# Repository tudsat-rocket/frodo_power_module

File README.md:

# Power Board

The battery board in our rockets.

### Components

- 3x 3000 mA h Sony VTC6 18650 lithium-ion cells in series

### Usage

| Connector           | Purpose                                                         |
| -----------         | --------------------------------------------------------------- |
| main switch         | + and - needs to be connected to enable the output on HC1, 2, 3 |
| HC1, 2, 3           | Power output                                                    |
| circumvent          | short + and - to supply power to Vmain without batteries directly from charge voltage |
| Vehicle Bus 1, 2    | Communication and bus power supply                              |

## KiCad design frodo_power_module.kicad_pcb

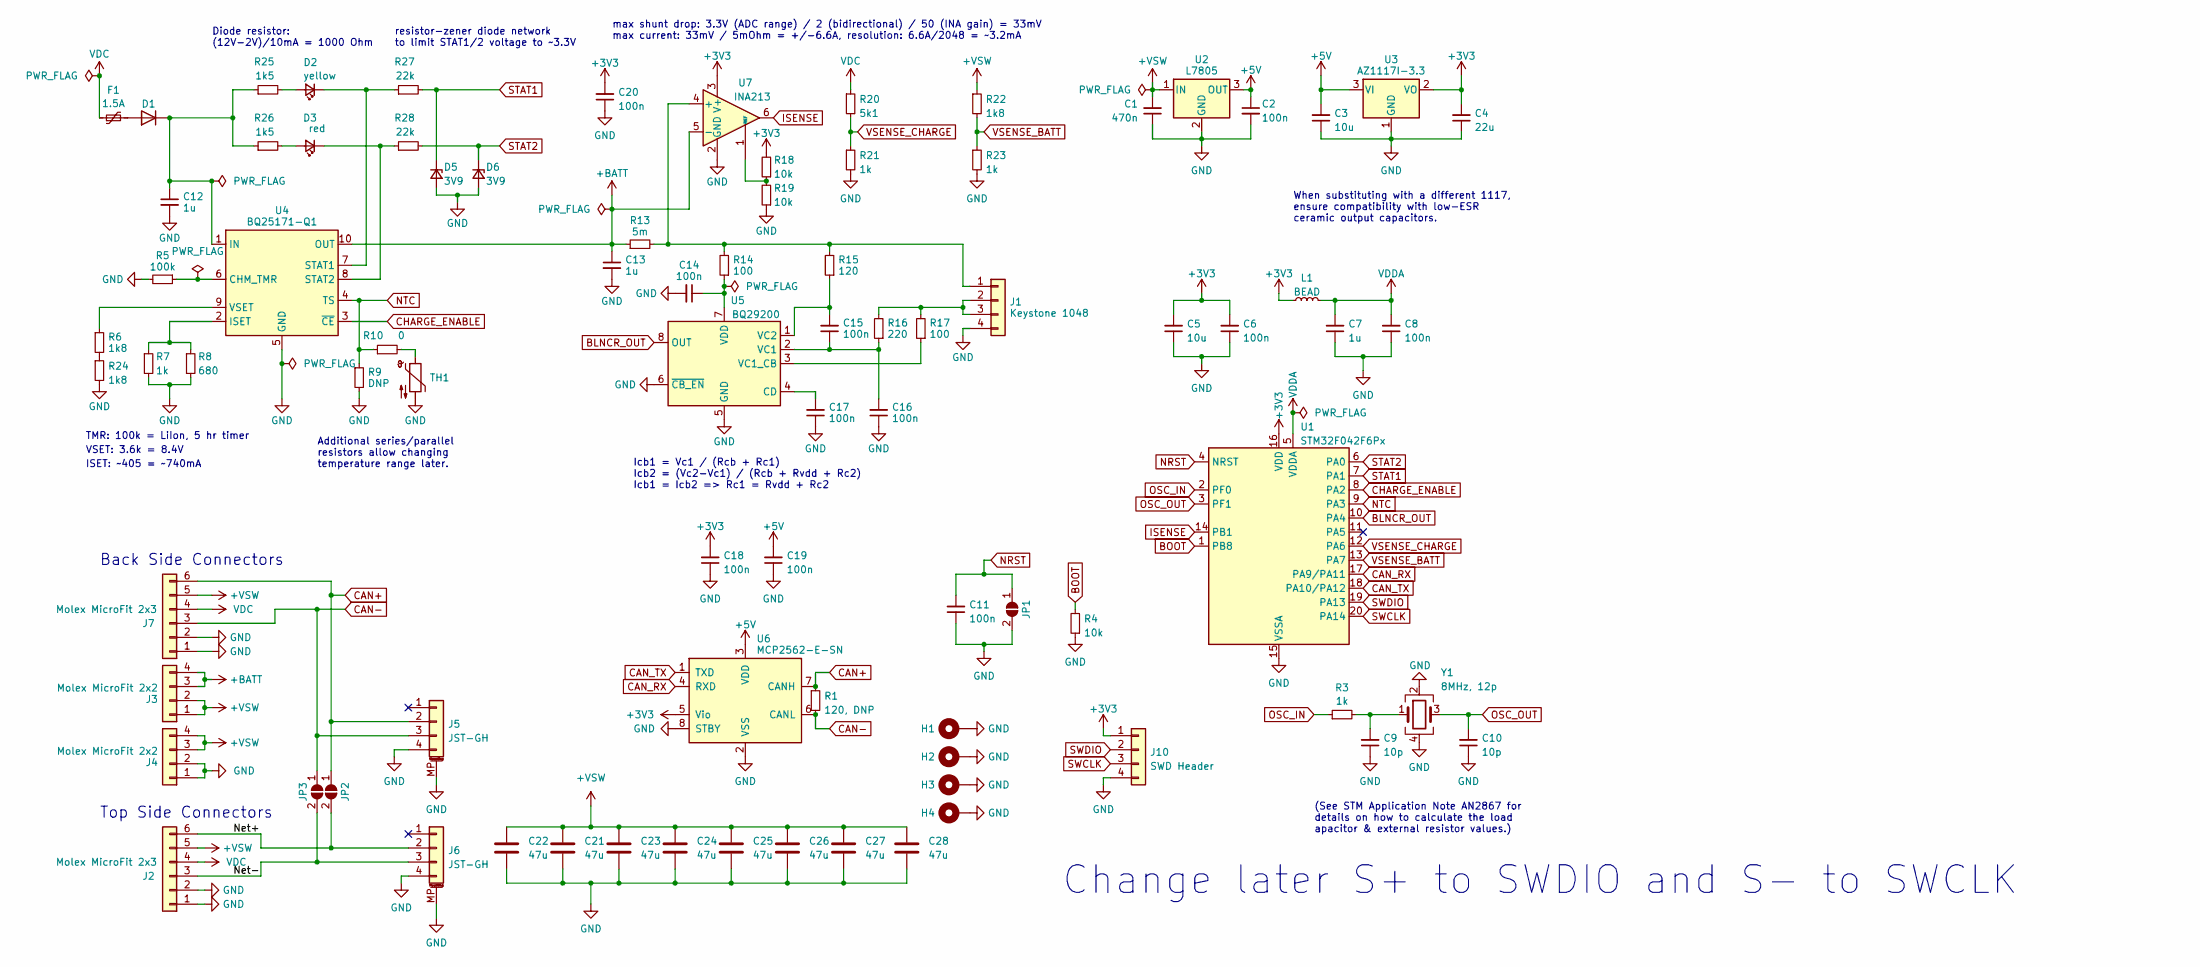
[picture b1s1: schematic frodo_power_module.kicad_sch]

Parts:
C1: 470n; C_0603_1608Metric; Part# CL10B474KA8NNNC; LCSC# C1623
C2, C6, C8, C11, C14, C15, C16, C17, C18, C19, C20: 100n; C_0603_1608Metric; Part# CC0603KRX7R9BB104; LCSC# C14663
C3, C5: 10u; C_1206_3216Metric; Part# CL31A106KBHNNNE; LCSC# C13585
C4: 22u; C_1206_3216Metric; Part# CL31A226KAHNNNE; LCSC# C12891
C7, C12, C13: 1u; C_0805_2012Metric; Part# CL21B105KBFNNNE; LCSC# C28323
C9, C10: 10p; C_0603_1608Metric; Part# CL10C100JB8NNNC; LCSC# C1634
C21, C22, C23, C24, C25, C26, C27, C28: 47u; C_1206_3216Metric
D1: D_SMA; Part# SS54; DigiKey# SK34A-LTPMSCT-ND
D2: yellow; LED_0603_1608Metric; Part# 19-213/Y2C-CQ2R2L/3T(CY); LCSC# C72038
D3: red; LED_0603_1608Metric; Part# KT-0603R; LCSC# C2286
D5, D6: 3V9; SOD323F_DIO; Part# D3Z3V9BF-7; LCSC# C444415
F1: 1.5A; Fuse_1206_3216Metric; Part# 0ZCJ0075AF2E; DigiKey# 507-1805-1-ND
H1, H2, H3, H4: MountingHole_Pad; MountingHole_3.2mm_M3_Pad_Via; Part# N/A; DigiKey# N/A
J1: Keystone 1048; keystone_1048; Part# 1048; DigiKey# 36-1098-ND
J2, J7: Molex MicroFit 2x3; Molex_Micro-Fit_3.0_43045-0600_2x03_P3.00mm_Horizontal; Part# 0430450600; LCSC# C127367
J3, J4: Molex MicroFit 2x2; Molex_Micro-Fit_3.0_43045-0400_2x02_P3.00mm_Horizontal; Part# 0430450400; LCSC# C122413
J5, J6: JST-GH; JST_GH_SM04B-GHS-TB_1x04-1MP_P1.25mm_Horizontal; Part# SM04B-GHS-TB; LCSC# C189895
J10: SWD Header; PinHeader_1x04_P2.54mm_Vertical; Part# N/A; DigiKey# N/A
JP1, JP2, JP3: r; SolderJumper-2_P1.3mm_Open_RoundedPad1.0x1.5mm; Part# N/A; DigiKey# N/A
L1: BEAD; L_0603_1608Metric; Part# GZ1608D601TF; LCSC# C1002
R1: 120, DNP; R_0603_1608Metric; Part# 0603WAF1200T5E; LCSC# C22787
R3, R7, R21, R23: 1k; R_0603_1608Metric; Part# 0603WAF1001T5E; LCSC# C21190
R4, R18, R19: 10k; R_0603_1608Metric; Part# 0603WAF1002T5E; LCSC# C25804
R5: 100k; R_0603_1608Metric; Part# 0603WAF1003T5E; LCSC# C25803
R6, R22, R24: 1k8; R_0603_1608Metric; Part# 0603WAF1801T5E; LCSC# C4177
R8: 680; R_0603_1608Metric; Part# 0603WAF6800T5E; LCSC# C23228
R9: DNP; R_0603_1608Metric; Part# N/A; LCSC# N/A
R10: 0; R_0603_1608Metric; Part# 0603WAF0000T5E; LCSC# C21189
R13: 5m; R_2512_6332Metric; Part# PA2512FKE7W0R005E; LCSC# C723630
R14, R17: 100; R_0603_1608Metric; Part# 0603WAF1000T5E; LCSC# C22775
R15: 120; R_0603_1608Metric; Part# 0603WAF1200T5E; LCSC# C22787
R16: 220; R_0603_1608Metric; Part# 0603WAF2200T5E; LCSC# C22962
R20: 5k1; R_0603_1608Metric; Part# 0603WAF5101T5E; LCSC# C23186
R25, R26: 1k5; R_0603_1608Metric; Part# 0603WAF1501T5E; LCSC# C22843
R27, R28: 22k; R_0603_1608Metric; Part# 0603WAF2202T5E; LCSC# C31850
TH1: NCU18XH103F6SRB; R_0603_1608Metric; Part# NCU18XH103F6SRB; DigiKey# 490-18139-1-ND
U1: STM32F042F6Px; TSSOP-20_4.4x6.5mm_P0.65mm; Part# STM32F042F6P6TR; DigiKey# 497-19656-1-ND
U2: L7805; TO-252-2; Part# L78M05ABDT-TR; LCSC# C58069
U3: AZ1117I-3.3; SOT-223-3_TabPin2; Part# AZ1117CH-3.3TRG1; LCSC# C92102
U4: BQ25171-Q1; Texas_S-PVSON-N10_ThermalVias; Part# BQ25171QWDRCRQ1; DigiKey# 296-BQ25171QWDRCRQ1CT-ND
U5: BQ29200; Texas_S-PVSON-N8_ThermalVias; Part# BQ29200DRBT; DigiKey# 296-32038-1-ND
U6: MCP2562-E-SN; SOIC-8_3.9x4.9mm_P1.27mm; Part# MCP2562-H/SN; DigiKey# MCP2562-H/SN
U7: INA213; SOT-363_SC-70-6; Part# INA213AIDCKR; DigiKey# 296-26072-1-ND
Y1: 8MHz, 12p; Crystal_SMD_5032-4Pin_5.0x3.2mm; Part# 5TJ480000NYLBC; DigiKey# 50-ECS-80-12-33-JGN-CT-ND

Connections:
+3V3: C4.2, C5.2, C6.2, C18.2, C20.2, J10.1, L1.1, R18.2, U1.16 (VDD), U3.2 (VO), U6.5 (Vio), U7.3 (V+)
+5V: C2.1, C3.2, C19.2, U2.3 (OUT), U3.3 (VI), U6.3 (VDD)
+BATT: C13.1, J3.3, J3.4, R13.1, U4.10 (OUT), U7.5 (-)
+VSW: C1.2, C21.1, C22.1, C23.1, C24.1, C25.1, C26.1, C27.1, C28.1, J2.5, J3.1, J3.2, J4.3, J4.4, J7.5, R22.1, U2.1 (IN)
/Net+: J2.6, J6.2, JP2.2 (B)
/Net-: J2.3, J6.3, JP3.2 (B)
BLNCR_OUT: U1.10 (PA4), U5.8 (OUT)
BOOT: R4.2, U1.1 (PB8)
CAN+: J5.2, J7.6, JP2.1 (A), R1.1, U6.7 (CANH)
CAN-: J5.3, J7.3, JP3.1 (A), R1.2, U6.6 (CANL)
CAN_RX: U1.17 (PA9/PA11), U6.4 (RXD)
CAN_TX: U1.18 (PA10/PA12), U6.1 (TXD)
CHARGE_ENABLE: U1.8 (PA2), U4.3 (~CE)
GND: C1.1, C2.2, C3.1, C4.1, C5.1, C6.1, C7.1, C8.1, C9.1, C10.1, C11.1, C12.2, C13.2, C14.2, C16.1, C17.1, C18.1, C19.1, C20.1, C21.2, C22.2, C23.2, C24.2, C25.2, C26.2, C27.2, C28.2, D5.2 (A), D6.2 (A), H1.1, H2.1, H3.1, H4.1, J1.4, J2.1, J2.2, J4.1, J4.2, J5.4, J5.MP (MountPin), J6.4, J6.MP (MountPin), J7.1, J7.2, J10.4, JP1.2 (B), R4.1, R5.2, R7.2, R8.2, R9.2, R19.1, R21.2, R23.2, R24.2, TH1.2, U1.15 (VSSA), U2.2 (GND), U3.1 (GND), U4.5 (GND), U4.11 (GND), U5.5 (GND), U5.6 (~CB_EN), U5.9 (PWR_PAD), U6.2 (VSS), U6.8 (STBY), U7.2 (GND), Y1.2, Y1.4
ISENSE: U1.14 (PB1), U7.6
NRST: C11.2, JP1.1 (A), U1.4 (NRST)
NTC: R9.1, R10.1, U1.9 (PA3), U4.4 (TS)
unnamed: C9.2, R3.2, Y1.1
unnamed: D1.2 (A), F1.2
unnamed: C12.1, D1.1 (K), R25.1, R26.1, U4.1 (IN)
unnamed: D2.2 (A), R25.2
unnamed: D2.1 (K), R27.1, U4.7 (STAT1)
unnamed: D3.2 (A), R26.2
unnamed: D3.1 (K), R28.1, U4.8 (STAT2)
unnamed: J1.1, R13.2, R14.2, R15.2, U7.4 (+)
unnamed: J1.2, J1.3, R16.2, R17.2
unnamed: R10.2, TH1.1
unnamed: R6.2, R24.1
unnamed: R5.1, U4.6 (CHM_TMR)
unnamed: R7.1, R8.1, U4.2 (ISET)
unnamed: R6.1, U4.9 (VSET)
unnamed: C17.2, U5.4 (CD)
unnamed: C15.1, C16.2, R16.1, U5.2 (VC1)
unnamed: R17.1, U5.3 (VC1_CB)
unnamed: C15.2, R15.1, U5.1 (VC2)
unnamed: C14.1, R14.1, U5.7 (VDD)
unnamed: R18.1, R19.2, U7.1 (REF)
OSC_IN: R3.1, U1.2 (PF0)
OSC_OUT: C10.2, U1.3 (PF1), Y1.3
STAT1: D5.1 (K), R27.2, U1.7 (PA1)
STAT2: D6.1 (K), R28.2, U1.6 (PA0)
SWCLK: J10.3, U1.20 (PA14)
SWDIO: J10.2, U1.19 (PA13)
VDC: F1.1, J2.4, J7.4, R20.1
VDDA: C7.2, C8.2, L1.2, U1.5 (VDDA)
VSENSE_BATT: R22.2, R23.1, U1.13 (PA7)
VSENSE_CHARGE: R20.2, R21.1, U1.12 (PA6)

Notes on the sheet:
(See STM Application Note AN2867 for details on how to calculate the load apacitor & external resistor values.)
Diode resistor: (12V-2V)/10mA = 1000 Ohm
Icb1 = Vc1 / (Rcb + Rc1) Icb2 = (Vc2-Vc1) / (Rcb + Rvdd + Rc2) Icb1 = Icb2 => Rc1 = Rvdd + Rc2
When substituting with a different 1117, ensure compatibility with low-ESR ceramic output capacitors.
max shunt drop: 3.3V (ADC range) / 2 (bidirectional) / 50 (INA gain) = 33mV max current: 33mV / 5mOhm = +/-6.6A, resolution: 6.6A/2048 = ~3.2mA
TMR: 100k = LiIon, 5 hr timer
Top Side Connectors
Back Side Connectors
VSET: 3.6k = 8.4V
Change later S+ to SWDIO and S- to SWCLK
Additional series/parallel resistors allow changing temperature range later.
ISET: ~405 = ~740mA
resistor-zener diode network to limit STAT1/2 voltage to ~3.3V

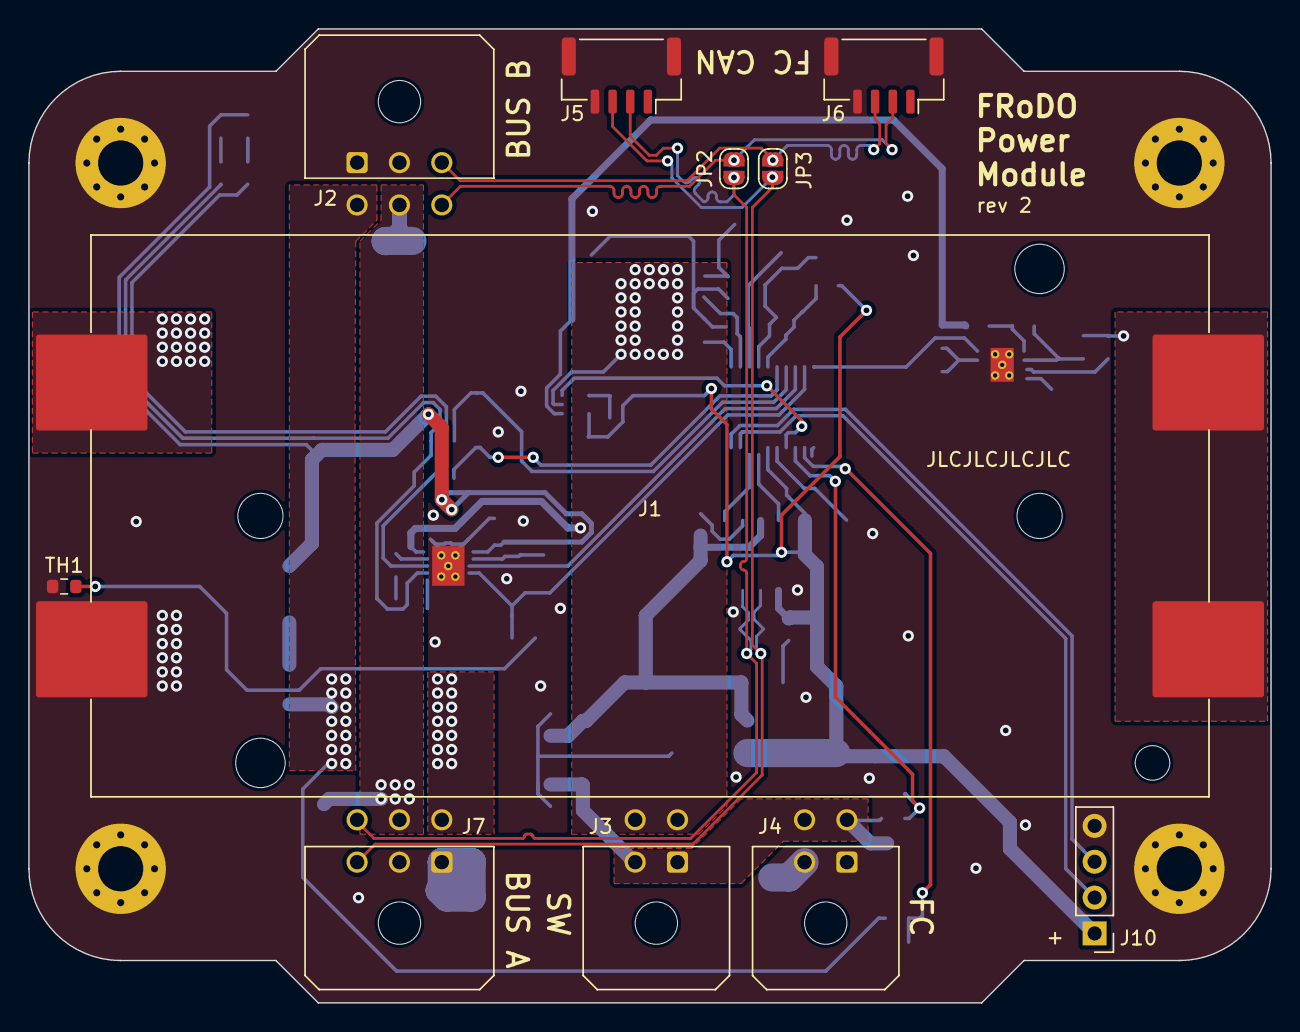
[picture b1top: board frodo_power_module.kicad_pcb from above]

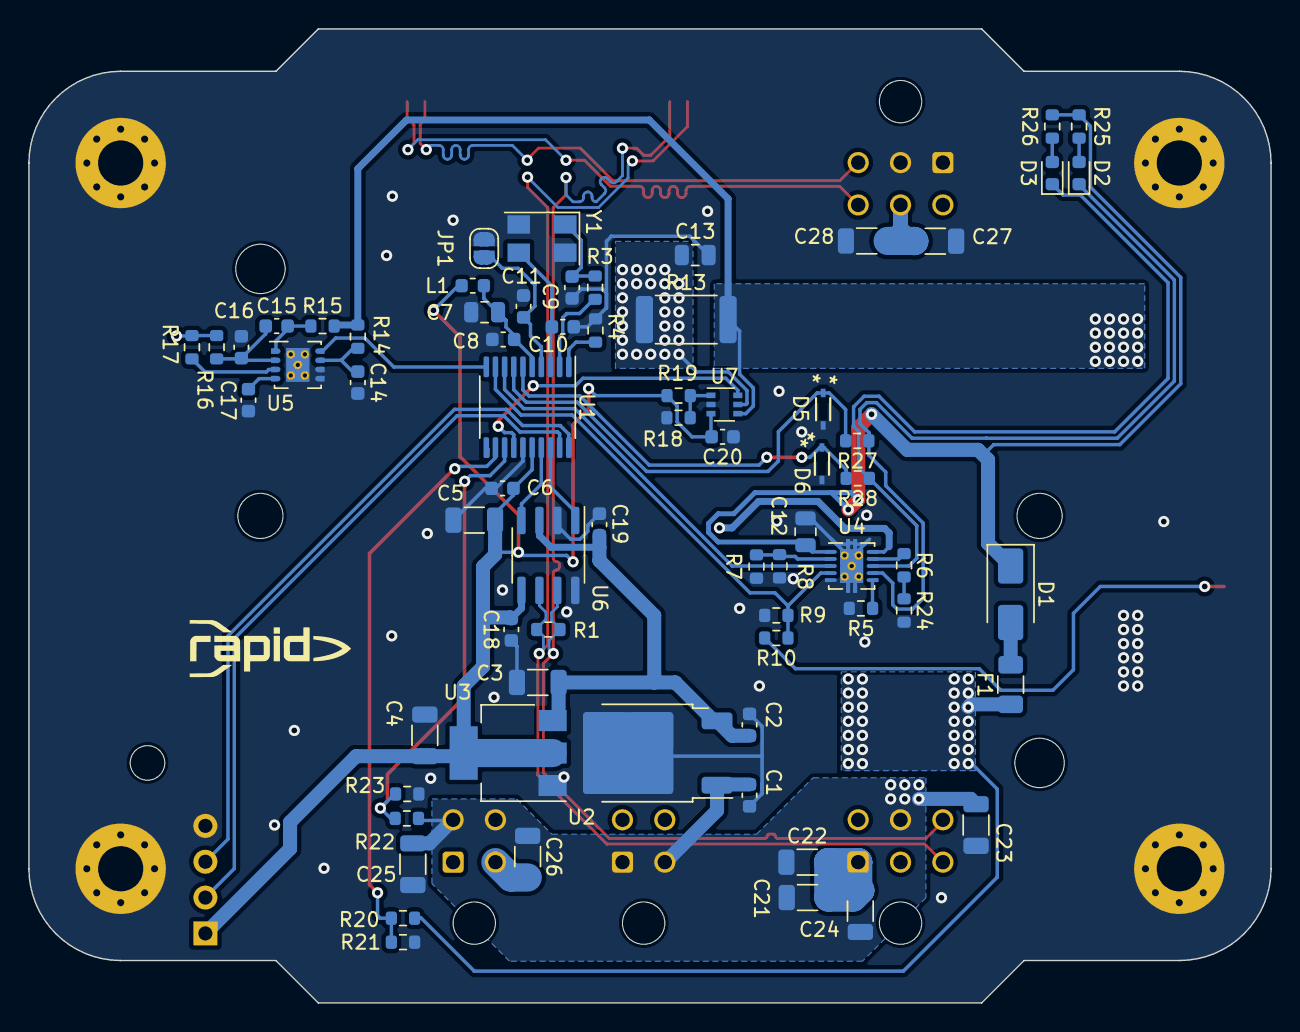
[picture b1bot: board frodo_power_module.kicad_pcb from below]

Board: 2 copper layers, 88.0 x 69.0 mm, 84 parts (69 on the bottom side), 47 nets.

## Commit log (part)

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2023-06-30 Add battery IC circuits
2023-06-30 Update PCB
2023-07-01 Fixed VSET for charger
2023-07-02 add current sense amp
2023-07-02 created component groups on pcb
2023-07-05 Add current sense amp to PCB
2023-07-09 changed PCB
2023-07-12 Update PCB design, add LEDs
2023-07-17 Add fuses to outputs, finish BOM
2023-10-19 Add firmware to repo
2023-11-07 removed breakwire system
2023-11-08 removed breakwire and changed Iset resistance from 440 to 390 to achieve approx 800mA charging
2023-12-03 modified schematic
2023-12-04 changed battery connector type, removed breakwrie, Iset resisrtor config and placed LEDS on main power supply
2023-12-04 removed other connectors
2023-12-05 Add review comments
2023-12-08 Review: Added resistor-zener diode network to limit voltage to STAT1/2 to ~3.3V
2023-12-11 changed connector Bezeichnet due to conflicts and made Keytore 1048 pads little bit bigger
2023-12-13 added power flags for ERC and removed all errors
2023-12-14 added footprints to D5 D7 J2 and J7. Needs review
2023-12-16 worked on pcb
2023-12-22 changed molex footprint from vertical to horiztontal
2023-12-23 Added Power Traces and made CAN+ and CAN- equal size
2023-12-23 worked on file
2023-12-23 saving work status
2023-12-23 saving work. Almost all routing is done. Ground plane will be added in the next steps to remove all errors and then the goal is to remove all warnings
2023-12-23 Only warning left to be removed. Also Jumper needs to be implemented and size or width of battery holder needs to be changed
2023-12-23 modified
2023-12-24 changed PIN layout to suggested one
2023-12-31 DRC check for hole to hole clerance and minimum trace to trace clearance also changed a few traces and zones
2023-12-31 changed zones
2024-01-10 Minor trace tweaks
2024-01-11 clear DRC msgs, align elements to grid
    After updating the design constraints according to the JLCPCB manufacturing capabilities, the PTHs
    of component U5 were to small (0.25mm diameter, min. is 0.3mm). Note that after resolving this error,
    the DRC now shows a warning about a modified footprint of U5.
2024-01-18 Replace parts with JLCPCB basic ones where possible, replace crystal footprint
2024-01-21 Minor routing changes, add outline
2024-01-25 added capacitors. By updating pcb the old Osci footprint was restored. This needs to be changed
2024-01-25 Add finishing touches, generate fabrication files
2024-02-01 Finalize BOM, CPL
2024-07-20 Update to shared_types CAN message, stable Rust
2024-09-27 Correct battery current CAN message type
